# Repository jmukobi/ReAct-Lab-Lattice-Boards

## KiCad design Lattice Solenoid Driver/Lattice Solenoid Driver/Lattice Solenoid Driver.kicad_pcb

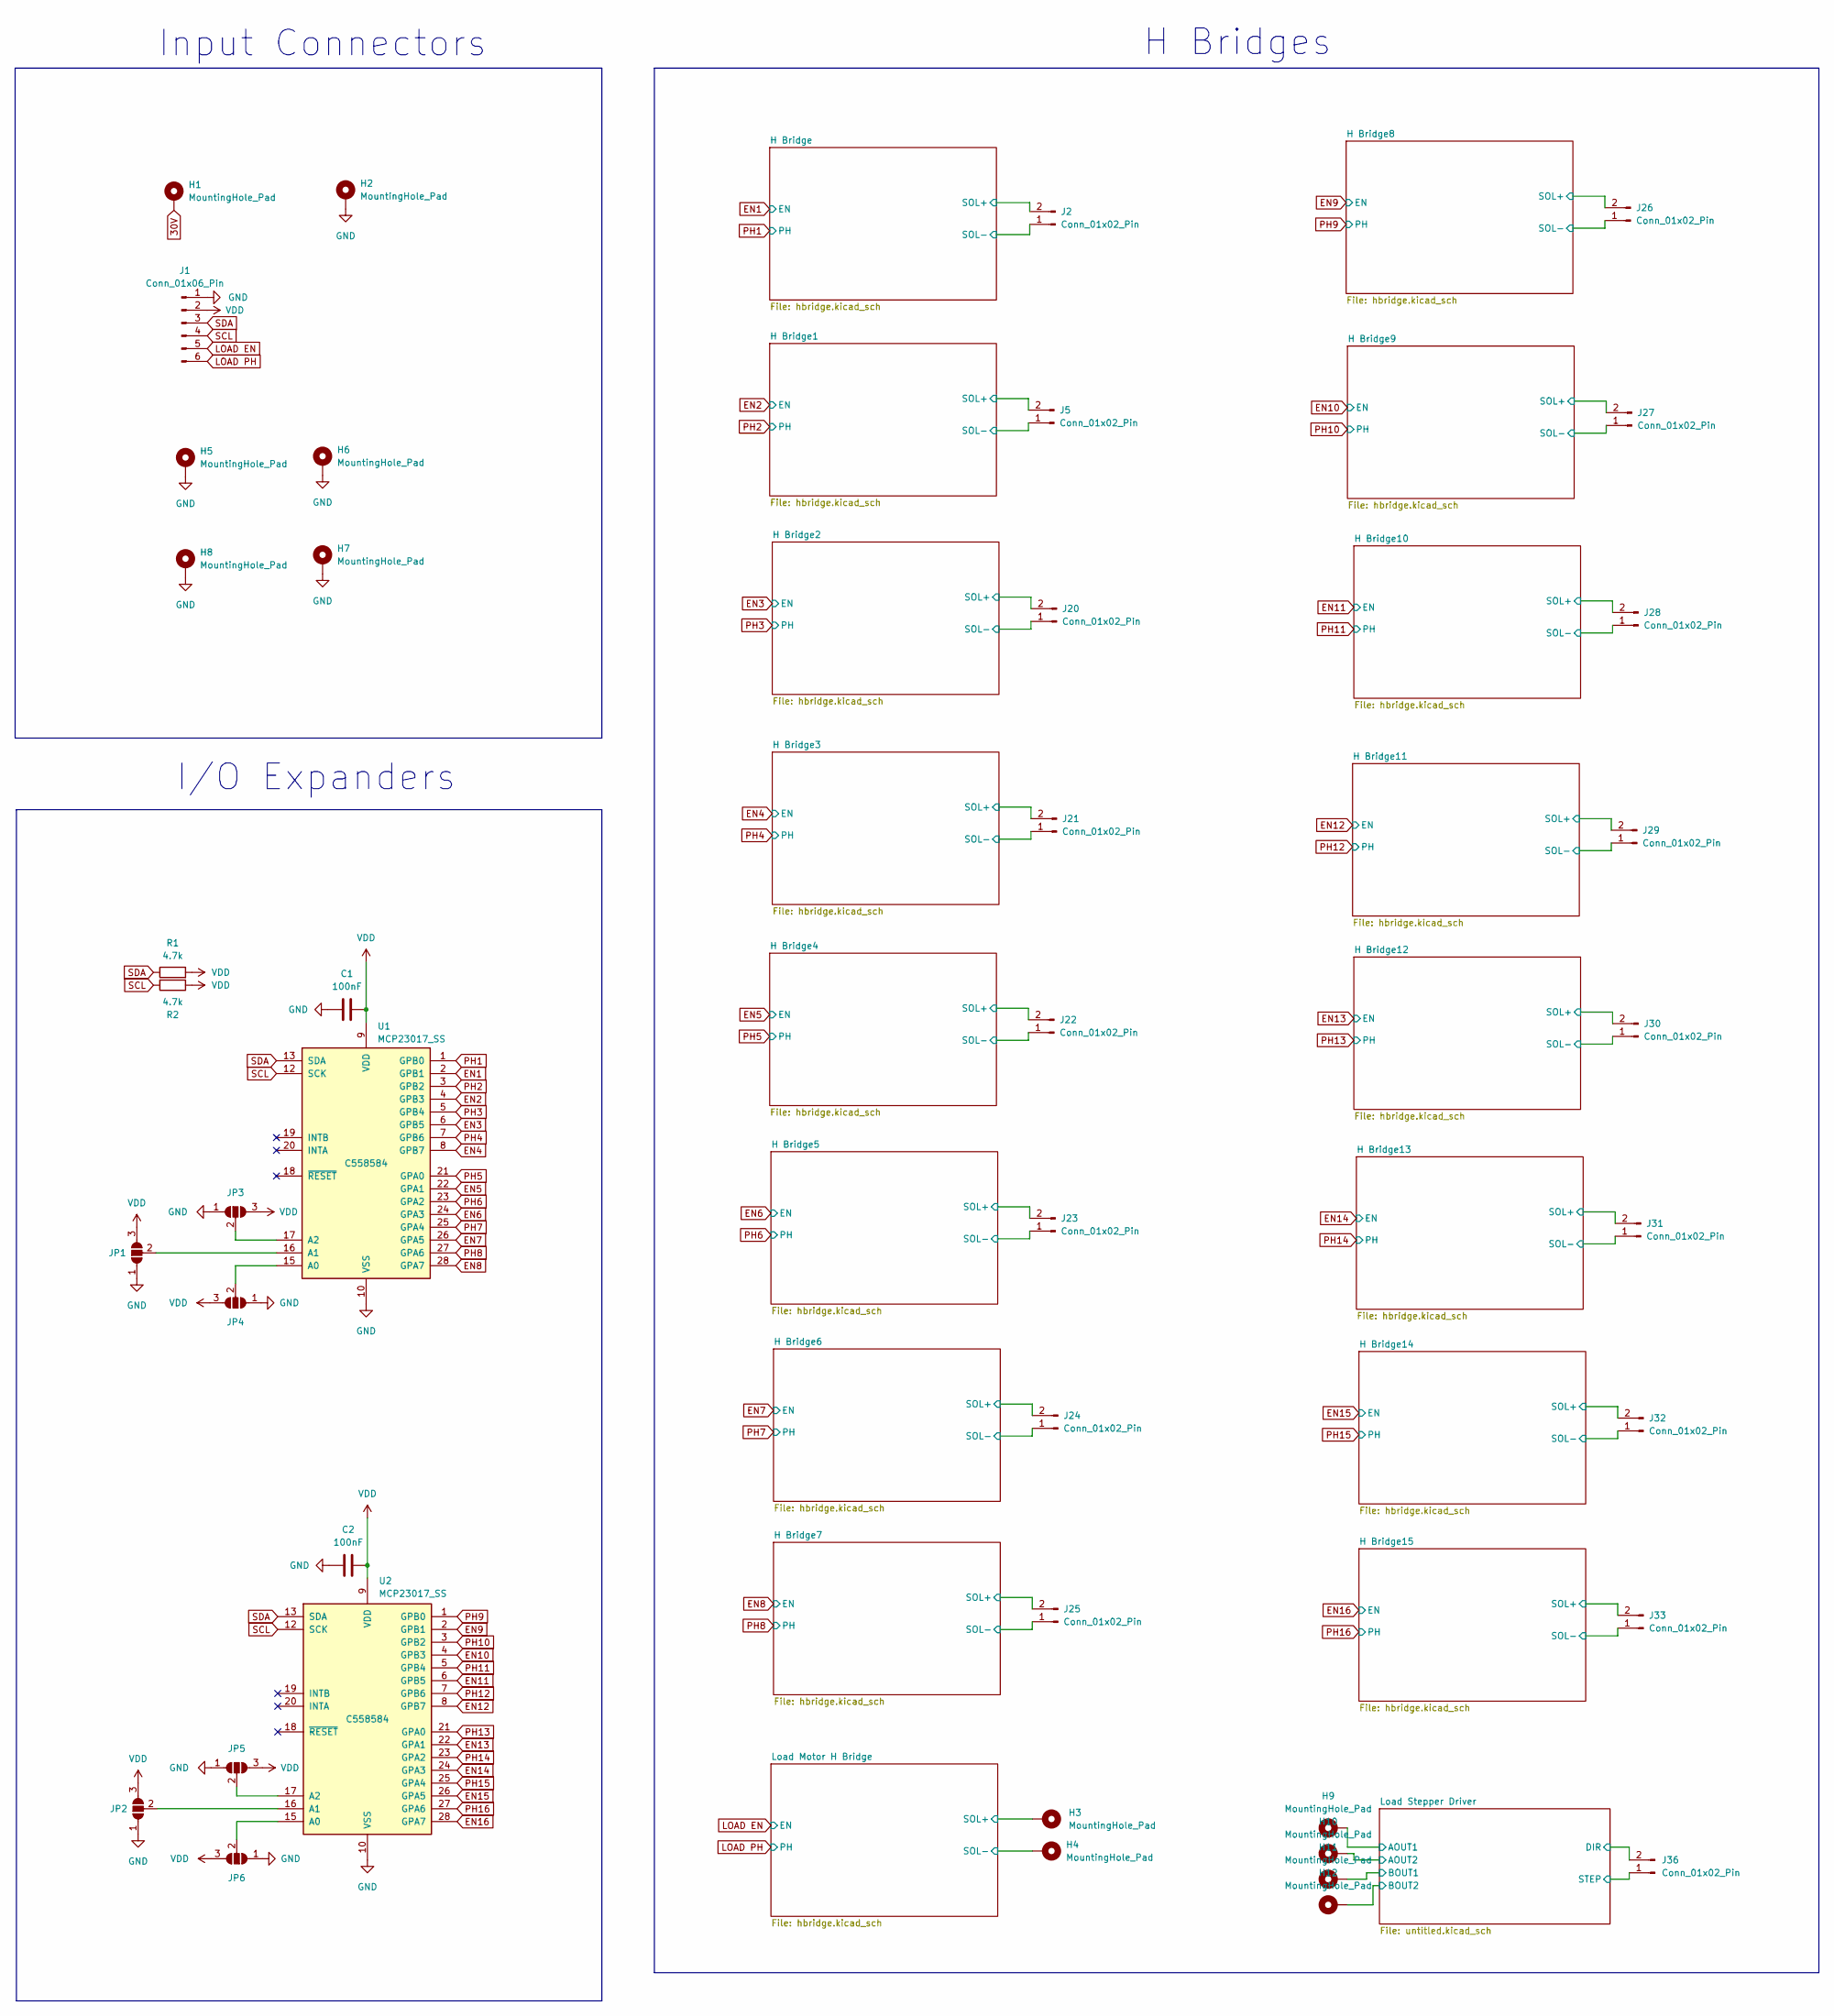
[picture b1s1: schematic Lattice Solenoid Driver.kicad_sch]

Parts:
C1, C2: 100nF; C_0805_2012Metric; Part # CC0805KRX7R9BB104
H1, H2, H3, H4, H5, H6, H7, H8, H9, H10, H11, H12: MountingHole_Pad; MountingHole_3.2mm_M3_DIN965_Pad_TopBottom
J1: Conn_01x06_Pin; PinHeader_1x06_P2.54mm_Vertical
J2, J5, J20, J21, J22, J23, J24, J25, J26, J27, J28, J29, J30, J31, J32, J33, J36: Conn_01x02_Pin; PinHeader_1x02_P2.54mm_Vertical
JP1, JP2, JP3, JP4, JP5, JP6: SolderJumper_3_Open; SolderJumper-3_P1.3mm_Open_RoundedPad1.0x1.5mm_NumberLabels
R1, R2: 4.7k; R_0805_2012Metric; Part # C17673
U1, U2: MCP23017_SS; SSOP-28_5.3x10.2mm_P0.65mm; Part # C558584

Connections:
30V: H1.1; also elsewhere on the board
/H Bridge1/SOL+: J5.2; also elsewhere on the board
/H Bridge1/SOL-: J5.1; also elsewhere on the board
/H Bridge2/SOL+: J20.2; also elsewhere on the board
/H Bridge2/SOL-: J20.1; also elsewhere on the board
/H Bridge3/SOL+: J21.2; also elsewhere on the board
/H Bridge3/SOL-: J21.1; also elsewhere on the board
/H Bridge4/SOL+: J22.2; also elsewhere on the board
/H Bridge4/SOL-: J22.1; also elsewhere on the board
/H Bridge5/SOL+: J23.2; also elsewhere on the board
/H Bridge5/SOL-: J23.1; also elsewhere on the board
/H Bridge6/SOL+: J24.2; also elsewhere on the board
/H Bridge6/SOL-: J24.1; also elsewhere on the board
/H Bridge7/SOL+: J25.2; also elsewhere on the board
/H Bridge7/SOL-: J25.1; also elsewhere on the board
/H Bridge8/SOL+: J26.2; also elsewhere on the board
/H Bridge8/SOL-: J26.1; also elsewhere on the board
/H Bridge9/SOL+: J27.2; also elsewhere on the board
/H Bridge9/SOL-: J27.1; also elsewhere on the board
/H Bridge10/SOL+: J28.2; also elsewhere on the board
/H Bridge10/SOL-: J28.1; also elsewhere on the board
/H Bridge11/SOL+: J29.2; also elsewhere on the board
/H Bridge11/SOL-: J29.1; also elsewhere on the board
/H Bridge12/SOL+: J30.2; also elsewhere on the board
/H Bridge12/SOL-: J30.1; also elsewhere on the board
/H Bridge13/SOL+: J31.2; also elsewhere on the board
/H Bridge13/SOL-: J31.1; also elsewhere on the board
/H Bridge14/SOL+: J32.2; also elsewhere on the board
/H Bridge14/SOL-: J32.1; also elsewhere on the board
/H Bridge15/SOL+: J33.2; also elsewhere on the board
/H Bridge15/SOL-: J33.1; also elsewhere on the board
/H Bridge/SOL+: J2.2; also elsewhere on the board
/H Bridge/SOL-: J2.1; also elsewhere on the board
/Load Motor H Bridge/SOL+: H3.1; also elsewhere on the board
/Load Motor H Bridge/SOL-: H4.1; also elsewhere on the board
/Load Stepper Driver/DIR: J36.2; also elsewhere on the board
/Load Stepper Driver/STEP: J36.1; also elsewhere on the board
EN1: U1.2 (GPB1); also elsewhere on the board
EN2: U1.4 (GPB3); also elsewhere on the board
EN3: U1.6 (GPB5); also elsewhere on the board
EN4: U1.8 (GPB7); also elsewhere on the board
EN5: U1.22 (GPA1); also elsewhere on the board
EN6: U1.24 (GPA3); also elsewhere on the board
EN7: U1.26 (GPA5); also elsewhere on the board
EN8: U1.28 (GPA7); also elsewhere on the board
EN9: U2.2 (GPB1); also elsewhere on the board
EN10: U2.4 (GPB3); also elsewhere on the board
EN11: U2.6 (GPB5); also elsewhere on the board
EN12: U2.8 (GPB7); also elsewhere on the board
EN13: U2.22 (GPA1); also elsewhere on the board
EN14: U2.24 (GPA3); also elsewhere on the board
EN15: U2.26 (GPA5); also elsewhere on the board
EN16: U2.28 (GPA7); also elsewhere on the board
GND: C1.1, C2.1, H2.1, H5.1, H6.1, H7.1, H8.1, J1.1, JP1.1 (A), JP2.1 (A), JP3.1 (A), JP4.1 (A), JP5.1 (A), JP6.1 (A), U1.10 (VSS), U2.10 (VSS); also elsewhere on the board
LOAD EN: J1.5; also elsewhere on the board
LOAD PH: J1.6; also elsewhere on the board
unnamed: JP1.2 (C), U1.16 (A1)
unnamed: JP2.2 (C), U2.16 (A1)
unnamed: JP3.2 (C), U1.17 (A2)
unnamed: JP4.2 (C), U1.15 (A0)
unnamed: JP5.2 (C), U2.17 (A2)
unnamed: JP6.2 (C), U2.15 (A0)
PH1: U1.1 (GPB0); also elsewhere on the board
PH2: U1.3 (GPB2); also elsewhere on the board
PH3: U1.5 (GPB4); also elsewhere on the board
PH4: U1.7 (GPB6); also elsewhere on the board
PH5: U1.21 (GPA0); also elsewhere on the board
PH6: U1.23 (GPA2); also elsewhere on the board
PH7: U1.25 (GPA4); also elsewhere on the board
PH8: U1.27 (GPA6); also elsewhere on the board
PH9: U2.1 (GPB0); also elsewhere on the board
PH10: U2.3 (GPB2); also elsewhere on the board
PH11: U2.5 (GPB4); also elsewhere on the board
PH12: U2.7 (GPB6); also elsewhere on the board
PH13: U2.21 (GPA0); also elsewhere on the board
PH14: U2.23 (GPA2); also elsewhere on the board
PH15: U2.25 (GPA4); also elsewhere on the board
PH16: U2.27 (GPA6); also elsewhere on the board
SCL: J1.4, R2.2, U1.12 (SCK), U2.12 (SCK)
SDA: J1.3, R1.1, U1.13 (SDA), U2.13 (SDA)
VDD: C1.2, C2.2, J1.2, JP1.3 (B), JP2.3 (B), JP3.3 (B), JP4.3 (B), JP5.3 (B), JP6.3 (B), R1.2, R2.1, U1.9 (VDD), U2.9 (VDD); also elsewhere on the board

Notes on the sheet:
H Bridges
I/O Expanders
Input Connectors

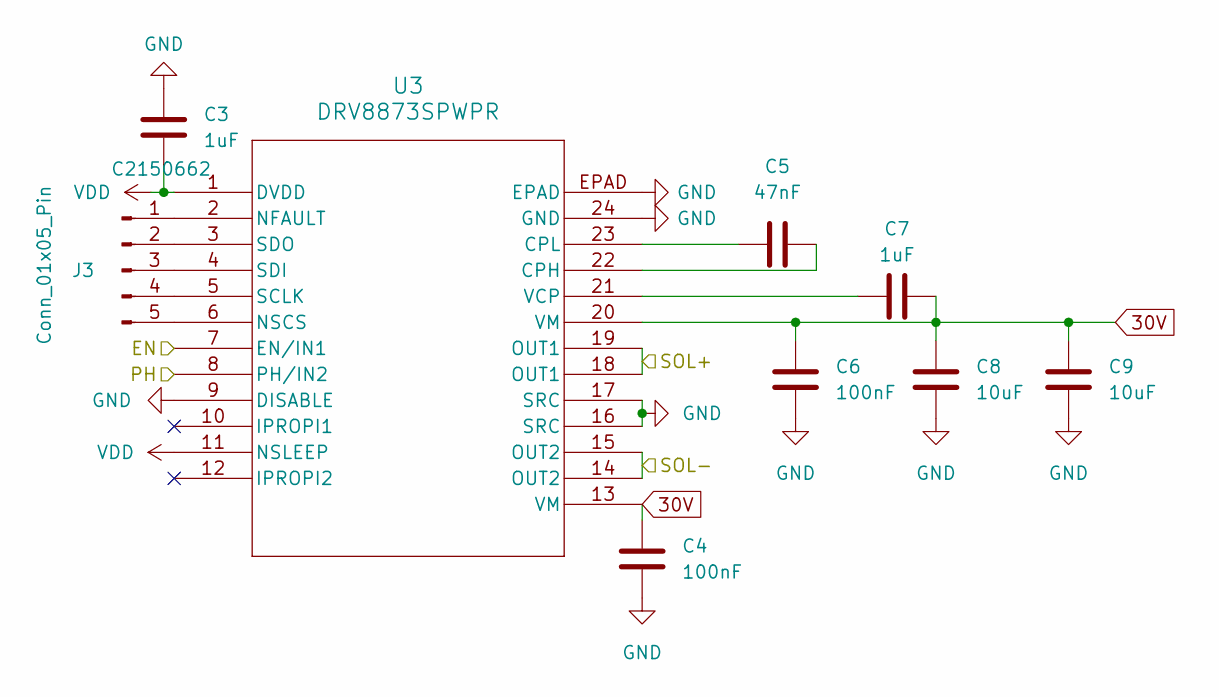
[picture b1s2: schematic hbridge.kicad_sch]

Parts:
C3, C7: 1uF; C_0805_2012Metric; Part # CL21B105KBFNNNE
C4, C6: 100nF; C_0805_2012Metric; Part # CC0805KRX7R9BB104
C5: 47nF; C_0805_2012Metric; Part # CL21B473KBCNNNC
C8, C9: 10uF; C_0805_2012Metric; Part # GRM21BR61H106KE43L
J3: Conn_01x05_Pin; PinHeader_1x05_P2.54mm_Vertical
U3: DRV8873SPWPR; PWP24_TEX; Part # C2150662

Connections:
30V: C4.1, C6.1, C7.2, C8.1, C9.1, U3.13 (VM), U3.20 (VM); also elsewhere on the board
/H Bridge/SOL+: U3.18 (OUT1), U3.19 (OUT1); also elsewhere on the board
/H Bridge/SOL-: U3.14 (OUT2), U3.15 (OUT2); also elsewhere on the board
EN1: U3.7 (EN/IN1); also elsewhere on the board
GND: C3.1, C4.2, C6.2, C8.2, C9.2, U3.9 (DISABLE), U3.16 (SRC), U3.17 (SRC), U3.24 (GND), U3.EPAD; also elsewhere on the board
unnamed: J3.1, U3.2 (NFAULT)
unnamed: J3.2, U3.3 (SDO)
unnamed: J3.3, U3.4 (SDI)
unnamed: J3.4, U3.5 (SCLK)
unnamed: J3.5, U3.6 (NSCS)
unnamed: C5.2, U3.22 (CPH)
unnamed: C5.1, U3.23 (CPL)
unnamed: C7.1, U3.21 (VCP)
PH1: U3.8 (PH/IN2); also elsewhere on the board
VDD: C3.2, U3.1 (DVDD), U3.11 (NSLEEP); also elsewhere on the board

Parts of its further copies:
C10, C14, C17, C21, C24, C28, C31, C35, C38, C42, C45, C49, C52, C56, C59, C63, C66, C70, C73, C77, C80, C84, C87, C91, C94, C98, C101, C105, C108, C112, C115, C119: 1uF; C_0805_2012Metric; Part # CL21B105KBFNNNE
C11, C13, C18, C20, C25, C27, C32, C34, C39, C41, C46, C48, C53, C55, C60, C62, C67, C69, C74, C76, C81, C83, C88, C90, C95, C97, C102, C104, C109, C111, C116, C118: 100nF; C_0805_2012Metric; Part # CC0805KRX7R9BB104
C12, C19, C26, C33, C40, C47, C54, C61, C68, C75, C82, C89, C96, C103, C110, C117: 47nF; C_0805_2012Metric; Part # CL21B473KBCNNNC
C15, C16, C22, C23, C29, C30, C36, C37, C43, C44, C50, C51, C57, C58, C64, C65, C71, C72, C78, C79, C85, C86, C92, C93, C99, C100, C106, C107, C113, C114, C120, C121: 10uF; C_0805_2012Metric; Part # GRM21BR61H106KE43L
J4, J6, J7, J8, J9, J10, J11, J12, J13, J14, J15, J16, J17, J18, J19, J34: Conn_01x05_Pin; PinHeader_1x05_P2.54mm_Vertical
U4, U5, U6, U7, U8, U9, U10, U11, U12, U13, U14, U15, U16, U17, U18, U19: DRV8873SPWPR; PWP24_TEX; Part # C2150662

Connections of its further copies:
30V: C11.1, C13.1, C14.2, C15.1, C16.1, C18.1, C20.1, C21.2, C22.1, C23.1, C25.1, C27.1, C28.2, C29.1, C30.1, C32.1, C34.1, C35.2, C36.1, C37.1, C39.1, C41.1, C42.2, C43.1, C44.1, C46.1, C48.1, C49.2, C50.1, C51.1, C53.1, C55.1, C56.2, C57.1, C58.1, C60.1, C62.1, C63.2, C64.1, C65.1, C67.1, C69.1, C70.2, C71.1, C72.1, C74.1, C76.1, C77.2, C78.1, C79.1, C81.1, C83.1, C84.2, C85.1, C86.1, C88.1, C90.1, C91.2, C92.1, C93.1, C95.1, C97.1, C98.2, C99.1, C100.1, C102.1, C104.1, C105.2, C106.1, C107.1, C109.1, C111.1, C112.2, C113.1, C114.1, C116.1, C118.1, C119.2, C120.1, C121.1, U4.13 (VM), U4.20 (VM), U5.13 (VM), U5.20 (VM), U6.13 (VM), U6.20 (VM), U7.13 (VM), U7.20 (VM), U8.13 (VM), U8.20 (VM), U9.13 (VM), U9.20 (VM), U10.13 (VM), U10.20 (VM), U11.13 (VM), U11.20 (VM), U12.13 (VM), U12.20 (VM), U13.13 (VM), U13.20 (VM), U14.13 (VM), U14.20 (VM), U15.13 (VM), U15.20 (VM), U16.13 (VM), U16.20 (VM), U17.13 (VM), U17.20 (VM), U18.13 (VM), U18.20 (VM), U19.13 (VM), U19.20 (VM); also elsewhere on the board
/H Bridge1/SOL+: U4.18 (OUT1), U4.19 (OUT1); also elsewhere on the board
/H Bridge1/SOL-: U4.14 (OUT2), U4.15 (OUT2); also elsewhere on the board
/H Bridge2/SOL+: U5.18 (OUT1), U5.19 (OUT1); also elsewhere on the board
/H Bridge2/SOL-: U5.14 (OUT2), U5.15 (OUT2); also elsewhere on the board
/H Bridge3/SOL+: U6.18 (OUT1), U6.19 (OUT1); also elsewhere on the board
/H Bridge3/SOL-: U6.14 (OUT2), U6.15 (OUT2); also elsewhere on the board
/H Bridge4/SOL+: U7.18 (OUT1), U7.19 (OUT1); also elsewhere on the board
/H Bridge4/SOL-: U7.14 (OUT2), U7.15 (OUT2); also elsewhere on the board
/H Bridge5/SOL+: U8.18 (OUT1), U8.19 (OUT1); also elsewhere on the board
/H Bridge5/SOL-: U8.14 (OUT2), U8.15 (OUT2); also elsewhere on the board
/H Bridge6/SOL+: U9.18 (OUT1), U9.19 (OUT1); also elsewhere on the board
/H Bridge6/SOL-: U9.14 (OUT2), U9.15 (OUT2); also elsewhere on the board
/H Bridge7/SOL+: U10.18 (OUT1), U10.19 (OUT1); also elsewhere on the board
/H Bridge7/SOL-: U10.14 (OUT2), U10.15 (OUT2); also elsewhere on the board
/H Bridge8/SOL+: U11.18 (OUT1), U11.19 (OUT1); also elsewhere on the board
/H Bridge8/SOL-: U11.14 (OUT2), U11.15 (OUT2); also elsewhere on the board
/H Bridge9/SOL+: U12.18 (OUT1), U12.19 (OUT1); also elsewhere on the board
/H Bridge9/SOL-: U12.14 (OUT2), U12.15 (OUT2); also elsewhere on the board
/H Bridge10/SOL+: U13.18 (OUT1), U13.19 (OUT1); also elsewhere on the board
/H Bridge10/SOL-: U13.14 (OUT2), U13.15 (OUT2); also elsewhere on the board
/H Bridge11/SOL+: U14.18 (OUT1), U14.19 (OUT1); also elsewhere on the board
/H Bridge11/SOL-: U14.14 (OUT2), U14.15 (OUT2); also elsewhere on the board
/H Bridge12/SOL+: U15.18 (OUT1), U15.19 (OUT1); also elsewhere on the board
/H Bridge12/SOL-: U15.14 (OUT2), U15.15 (OUT2); also elsewhere on the board
/H Bridge13/SOL+: U16.18 (OUT1), U16.19 (OUT1); also elsewhere on the board
/H Bridge13/SOL-: U16.14 (OUT2), U16.15 (OUT2); also elsewhere on the board
/H Bridge14/SOL+: U17.18 (OUT1), U17.19 (OUT1); also elsewhere on the board
/H Bridge14/SOL-: U17.14 (OUT2), U17.15 (OUT2); also elsewhere on the board
/H Bridge15/SOL+: U18.18 (OUT1), U18.19 (OUT1); also elsewhere on the board
/H Bridge15/SOL-: U18.14 (OUT2), U18.15 (OUT2); also elsewhere on the board
/Load Motor H Bridge/SOL+: U19.18 (OUT1), U19.19 (OUT1); also elsewhere on the board
/Load Motor H Bridge/SOL-: U19.14 (OUT2), U19.15 (OUT2); also elsewhere on the board
EN2: U4.7 (EN/IN1); also elsewhere on the board
EN3: U5.7 (EN/IN1); also elsewhere on the board
EN4: U6.7 (EN/IN1); also elsewhere on the board
EN5: U7.7 (EN/IN1); also elsewhere on the board
EN6: U8.7 (EN/IN1); also elsewhere on the board
EN7: U9.7 (EN/IN1); also elsewhere on the board
EN8: U10.7 (EN/IN1); also elsewhere on the board
EN9: U11.7 (EN/IN1); also elsewhere on the board
EN10: U12.7 (EN/IN1); also elsewhere on the board
EN11: U13.7 (EN/IN1); also elsewhere on the board
EN12: U14.7 (EN/IN1); also elsewhere on the board
EN13: U15.7 (EN/IN1); also elsewhere on the board
EN14: U16.7 (EN/IN1); also elsewhere on the board
EN15: U17.7 (EN/IN1); also elsewhere on the board
EN16: U18.7 (EN/IN1); also elsewhere on the board
GND: C10.1, C11.2, C13.2, C15.2, C16.2, C17.1, C18.2, C20.2, C22.2, C23.2, C24.1, C25.2, C27.2, C29.2, C30.2, C31.1, C32.2, C34.2, C36.2, C37.2, C38.1, C39.2, C41.2, C43.2, C44.2, C45.1, C46.2, C48.2, C50.2, C51.2, C52.1, C53.2, C55.2, C57.2, C58.2, C59.1, C60.2, C62.2, C64.2, C65.2, C66.1, C67.2, C69.2, C71.2, C72.2, C73.1, C74.2, C76.2, C78.2, C79.2, C80.1, C81.2, C83.2, C85.2, C86.2, C87.1, C88.2, C90.2, C92.2, C93.2, C94.1, C95.2, C97.2, C99.2, C100.2, C101.1, C102.2, C104.2, C106.2, C107.2, C108.1, C109.2, C111.2, C113.2, C114.2, C115.1, C116.2, C118.2, C120.2, C121.2, U4.9 (DISABLE), U4.16 (SRC), U4.17 (SRC), U4.24 (GND), U4.EPAD, U5.9 (DISABLE), U5.16 (SRC), U5.17 (SRC), U5.24 (GND), U5.EPAD, U6.9 (DISABLE), U6.16 (SRC), U6.17 (SRC), U6.24 (GND), U6.EPAD, U7.9 (DISABLE), U7.16 (SRC), U7.17 (SRC), U7.24 (GND), U7.EPAD, U8.9 (DISABLE), U8.16 (SRC), U8.17 (SRC), U8.24 (GND), U8.EPAD, U9.9 (DISABLE), U9.16 (SRC), U9.17 (SRC), U9.24 (GND), U9.EPAD, U10.9 (DISABLE), U10.16 (SRC), U10.17 (SRC), U10.24 (GND), U10.EPAD, U11.9 (DISABLE), U11.16 (SRC), U11.17 (SRC), U11.24 (GND), U11.EPAD, U12.9 (DISABLE), U12.16 (SRC), U12.17 (SRC), U12.24 (GND), U12.EPAD, U13.9 (DISABLE), U13.16 (SRC), U13.17 (SRC), U13.24 (GND), U13.EPAD, U14.9 (DISABLE), U14.16 (SRC), U14.17 (SRC), U14.24 (GND), U14.EPAD, U15.9 (DISABLE), U15.16 (SRC), U15.17 (SRC), U15.24 (GND), U15.EPAD, U16.9 (DISABLE), U16.16 (SRC), U16.17 (SRC), U16.24 (GND), U16.EPAD, U17.9 (DISABLE), U17.16 (SRC), U17.17 (SRC), U17.24 (GND), U17.EPAD, U18.9 (DISABLE), U18.16 (SRC), U18.17 (SRC), U18.24 (GND), U18.EPAD, U19.9 (DISABLE), U19.16 (SRC), U19.17 (SRC), U19.24 (GND), U19.EPAD; also elsewhere on the board
LOAD EN: U19.7 (EN/IN1); also elsewhere on the board
LOAD PH: U19.8 (PH/IN2); also elsewhere on the board
unnamed: J4.1, U4.2 (NFAULT)
unnamed: J4.2, U4.3 (SDO)
unnamed: J4.3, U4.4 (SDI)
unnamed: J4.4, U4.5 (SCLK)
unnamed: J4.5, U4.6 (NSCS)
unnamed: J6.1, U5.2 (NFAULT)
unnamed: J6.2, U5.3 (SDO)
unnamed: J6.3, U5.4 (SDI)
unnamed: J6.4, U5.5 (SCLK)
unnamed: J6.5, U5.6 (NSCS)
unnamed: J7.1, U6.2 (NFAULT)
unnamed: J7.2, U6.3 (SDO)
unnamed: J7.3, U6.4 (SDI)
unnamed: J7.4, U6.5 (SCLK)
unnamed: J7.5, U6.6 (NSCS)
unnamed: J8.1, U7.2 (NFAULT)
unnamed: J8.2, U7.3 (SDO)
unnamed: J8.3, U7.4 (SDI)
unnamed: J8.4, U7.5 (SCLK)
unnamed: J8.5, U7.6 (NSCS)
unnamed: J9.1, U8.2 (NFAULT)
unnamed: J9.2, U8.3 (SDO)
unnamed: J9.3, U8.4 (SDI)
unnamed: J9.4, U8.5 (SCLK)
unnamed: J9.5, U8.6 (NSCS)
unnamed: J10.1, U9.2 (NFAULT)
unnamed: J10.2, U9.3 (SDO)
unnamed: J10.3, U9.4 (SDI)
unnamed: J10.4, U9.5 (SCLK)
unnamed: J10.5, U9.6 (NSCS)
unnamed: J11.1, U10.2 (NFAULT)
unnamed: J11.2, U10.3 (SDO)
unnamed: J11.3, U10.4 (SDI)
unnamed: J11.4, U10.5 (SCLK)
unnamed: J11.5, U10.6 (NSCS)
unnamed: J12.1, U11.2 (NFAULT)
unnamed: J12.2, U11.3 (SDO)
unnamed: J12.3, U11.4 (SDI)
unnamed: J12.4, U11.5 (SCLK)
unnamed: J12.5, U11.6 (NSCS)
unnamed: J13.1, U12.2 (NFAULT)
unnamed: J13.2, U12.3 (SDO)
unnamed: J13.3, U12.4 (SDI)
unnamed: J13.4, U12.5 (SCLK)
unnamed: J13.5, U12.6 (NSCS)
unnamed: J14.1, U13.2 (NFAULT)
unnamed: J14.2, U13.3 (SDO)
unnamed: J14.3, U13.4 (SDI)
unnamed: J14.4, U13.5 (SCLK)
unnamed: J14.5, U13.6 (NSCS)
unnamed: J15.1, U14.2 (NFAULT)
unnamed: J15.2, U14.3 (SDO)
unnamed: J15.3, U14.4 (SDI)
unnamed: J15.4, U14.5 (SCLK)
unnamed: J15.5, U14.6 (NSCS)
unnamed: J16.1, U15.2 (NFAULT)
unnamed: J16.2, U15.3 (SDO)
unnamed: J16.3, U15.4 (SDI)
unnamed: J16.4, U15.5 (SCLK)
unnamed: J16.5, U15.6 (NSCS)
unnamed: J17.1, U16.2 (NFAULT)
unnamed: J17.2, U16.3 (SDO)
unnamed: J17.3, U16.4 (SDI)
unnamed: J17.4, U16.5 (SCLK)
unnamed: J17.5, U16.6 (NSCS)
unnamed: J18.1, U17.2 (NFAULT)
unnamed: J18.2, U17.3 (SDO)
unnamed: J18.3, U17.4 (SDI)
unnamed: J18.4, U17.5 (SCLK)
unnamed: J18.5, U17.6 (NSCS)
unnamed: J19.1, U18.2 (NFAULT)
unnamed: J19.2, U18.3 (SDO)
unnamed: J19.3, U18.4 (SDI)
unnamed: J19.4, U18.5 (SCLK)
unnamed: J19.5, U18.6 (NSCS)
unnamed: J34.1, U19.2 (NFAULT)
unnamed: J34.2, U19.3 (SDO)
unnamed: J34.3, U19.4 (SDI)
unnamed: J34.4, U19.5 (SCLK)
unnamed: J34.5, U19.6 (NSCS)
unnamed: C12.2, U4.22 (CPH)
unnamed: C12.1, U4.23 (CPL)
unnamed: C14.1, U4.21 (VCP)
unnamed: C19.2, U5.22 (CPH)
unnamed: C19.1, U5.23 (CPL)
unnamed: C21.1, U5.21 (VCP)
unnamed: C26.2, U6.22 (CPH)
unnamed: C26.1, U6.23 (CPL)
unnamed: C28.1, U6.21 (VCP)
unnamed: C33.2, U7.22 (CPH)
unnamed: C33.1, U7.23 (CPL)
unnamed: C35.1, U7.21 (VCP)
unnamed: C40.2, U8.22 (CPH)
unnamed: C40.1, U8.23 (CPL)
unnamed: C42.1, U8.21 (VCP)
unnamed: C47.2, U9.22 (CPH)
unnamed: C47.1, U9.23 (CPL)
unnamed: C49.1, U9.21 (VCP)
unnamed: C54.2, U10.22 (CPH)
unnamed: C54.1, U10.23 (CPL)
unnamed: C56.1, U10.21 (VCP)
unnamed: C61.2, U11.22 (CPH)
unnamed: C61.1, U11.23 (CPL)
unnamed: C63.1, U11.21 (VCP)
unnamed: C68.2, U12.22 (CPH)
unnamed: C68.1, U12.23 (CPL)
unnamed: C70.1, U12.21 (VCP)
unnamed: C75.2, U13.22 (CPH)
unnamed: C75.1, U13.23 (CPL)
unnamed: C77.1, U13.21 (VCP)
unnamed: C82.2, U14.22 (CPH)
unnamed: C82.1, U14.23 (CPL)
unnamed: C84.1, U14.21 (VCP)
unnamed: C89.2, U15.22 (CPH)
unnamed: C89.1, U15.23 (CPL)
unnamed: C91.1, U15.21 (VCP)
unnamed: C96.2, U16.22 (CPH)
unnamed: C96.1, U16.23 (CPL)
unnamed: C98.1, U16.21 (VCP)
unnamed: C103.2, U17.22 (CPH)
unnamed: C103.1, U17.23 (CPL)
unnamed: C105.1, U17.21 (VCP)
unnamed: C110.2, U18.22 (CPH)
unnamed: C110.1, U18.23 (CPL)
unnamed: C112.1, U18.21 (VCP)
unnamed: C117.2, U19.22 (CPH)
unnamed: C117.1, U19.23 (CPL)
unnamed: C119.1, U19.21 (VCP)
PH2: U4.8 (PH/IN2); also elsewhere on the board
PH3: U5.8 (PH/IN2); also elsewhere on the board
PH4: U6.8 (PH/IN2); also elsewhere on the board
PH5: U7.8 (PH/IN2); also elsewhere on the board
PH6: U8.8 (PH/IN2); also elsewhere on the board
PH7: U9.8 (PH/IN2); also elsewhere on the board
PH8: U10.8 (PH/IN2); also elsewhere on the board
PH9: U11.8 (PH/IN2); also elsewhere on the board
PH10: U12.8 (PH/IN2); also elsewhere on the board
PH11: U13.8 (PH/IN2); also elsewhere on the board
PH12: U14.8 (PH/IN2); also elsewhere on the board
PH13: U15.8 (PH/IN2); also elsewhere on the board
PH14: U16.8 (PH/IN2); also elsewhere on the board
PH15: U17.8 (PH/IN2); also elsewhere on the board
PH16: U18.8 (PH/IN2); also elsewhere on the board
VDD: C10.2, C17.2, C24.2, C31.2, C38.2, C45.2, C52.2, C59.2, C66.2, C73.2, C80.2, C87.2, C94.2, C101.2, C108.2, C115.2, U4.1 (DVDD), U4.11 (NSLEEP), U5.1 (DVDD), U5.11 (NSLEEP), U6.1 (DVDD), U6.11 (NSLEEP), U7.1 (DVDD), U7.11 (NSLEEP), U8.1 (DVDD), U8.11 (NSLEEP), U9.1 (DVDD), U9.11 (NSLEEP), U10.1 (DVDD), U10.11 (NSLEEP), U11.1 (DVDD), U11.11 (NSLEEP), U12.1 (DVDD), U12.11 (NSLEEP), U13.1 (DVDD), U13.11 (NSLEEP), U14.1 (DVDD), U14.11 (NSLEEP), U15.1 (DVDD), U15.11 (NSLEEP), U16.1 (DVDD), U16.11 (NSLEEP), U17.1 (DVDD), U17.11 (NSLEEP), U18.1 (DVDD), U18.11 (NSLEEP), U19.1 (DVDD), U19.11 (NSLEEP); also elsewhere on the board

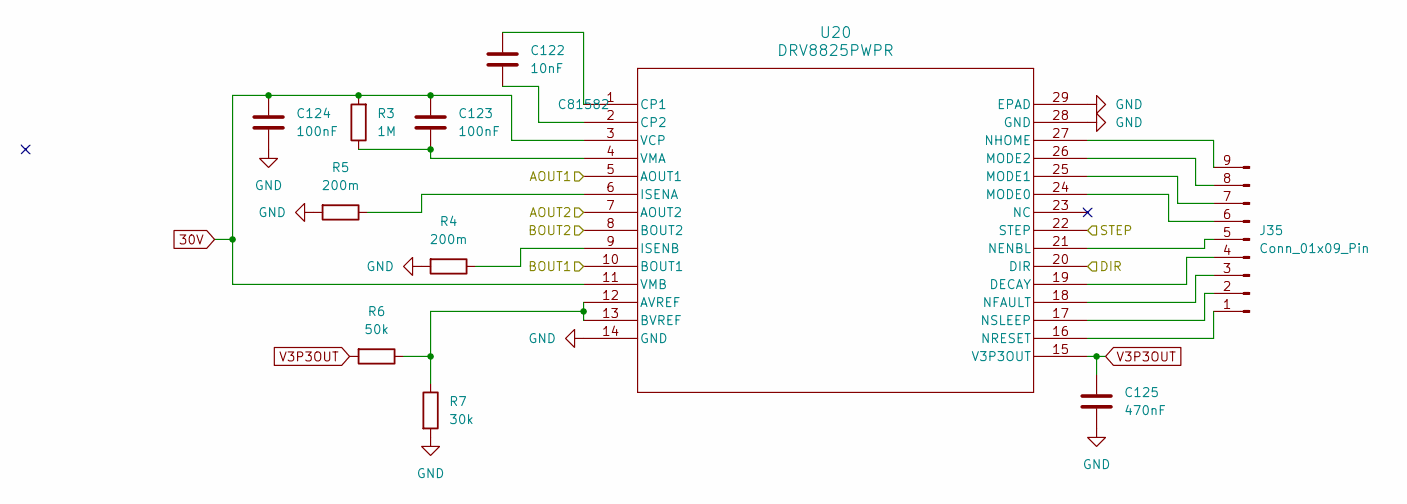
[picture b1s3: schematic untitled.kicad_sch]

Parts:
C122: 10nF; C_0805_2012Metric; Part # CC0805KRX7R9BB104
C123, C124: 100nF; C_0805_2012Metric; Part # CC0805KRX7R9BB104
C125: 470nF; C_0805_2012Metric; Part # CC0805KRX7R9BB104
J35: Conn_01x09_Pin; PinHeader_1x09_P2.54mm_Vertical
R3: 1M; R_0805_2012Metric; Part # C17673
R4, R5: 200m; R_0805_2012Metric; Part # C17673
R6: 50k; R_0805_2012Metric; Part # C17673
R7: 30k; R_0805_2012Metric; Part # C17673
U20: DRV8825PWPR; PWP28_5P18X3P1; Part # C81582

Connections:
30V: C123.1, C124.1, R3.2, U20.3 (VCP), U20.11 (VMB); also elsewhere on the board
/Load Stepper Driver/AOUT1: U20.5 (AOUT1); also elsewhere on the board
/Load Stepper Driver/AOUT2: U20.7 (AOUT2); also elsewhere on the board
/Load Stepper Driver/BOUT1: U20.10 (BOUT1); also elsewhere on the board
/Load Stepper Driver/BOUT2: U20.8 (BOUT2); also elsewhere on the board
/Load Stepper Driver/DIR: U20.20 (DIR); also elsewhere on the board
/Load Stepper Driver/STEP: U20.22 (STEP); also elsewhere on the board
GND: C124.2, C125.2, R4.2, R5.2, R7.2, U20.14 (GND), U20.28 (GND), U20.29 (EPAD); also elsewhere on the board
unnamed: J35.1, U20.16 (NRESET)
unnamed: J35.2, U20.17 (NSLEEP)
unnamed: J35.3, U20.18 (NFAULT)
unnamed: J35.4, U20.19 (DECAY)
unnamed: J35.5, U20.21 (NENBL)
unnamed: J35.6, U20.24 (MODE0)
unnamed: J35.7, U20.25 (MODE1)
unnamed: J35.8, U20.26 (MODE2)
unnamed: J35.9, U20.27 (NHOME)
unnamed: R6.1, R7.1, U20.12 (AVREF), U20.13 (BVREF)
unnamed: C122.1, U20.1 (CP1)
unnamed: C122.2, U20.2 (CP2)
unnamed: R5.1, U20.6 (ISENA)
unnamed: R4.1, U20.9 (ISENB)
unnamed: C123.2, R3.1, U20.4 (VMA)
V3P3OUT: C125.1, R6.2, U20.15 (V3P3OUT)

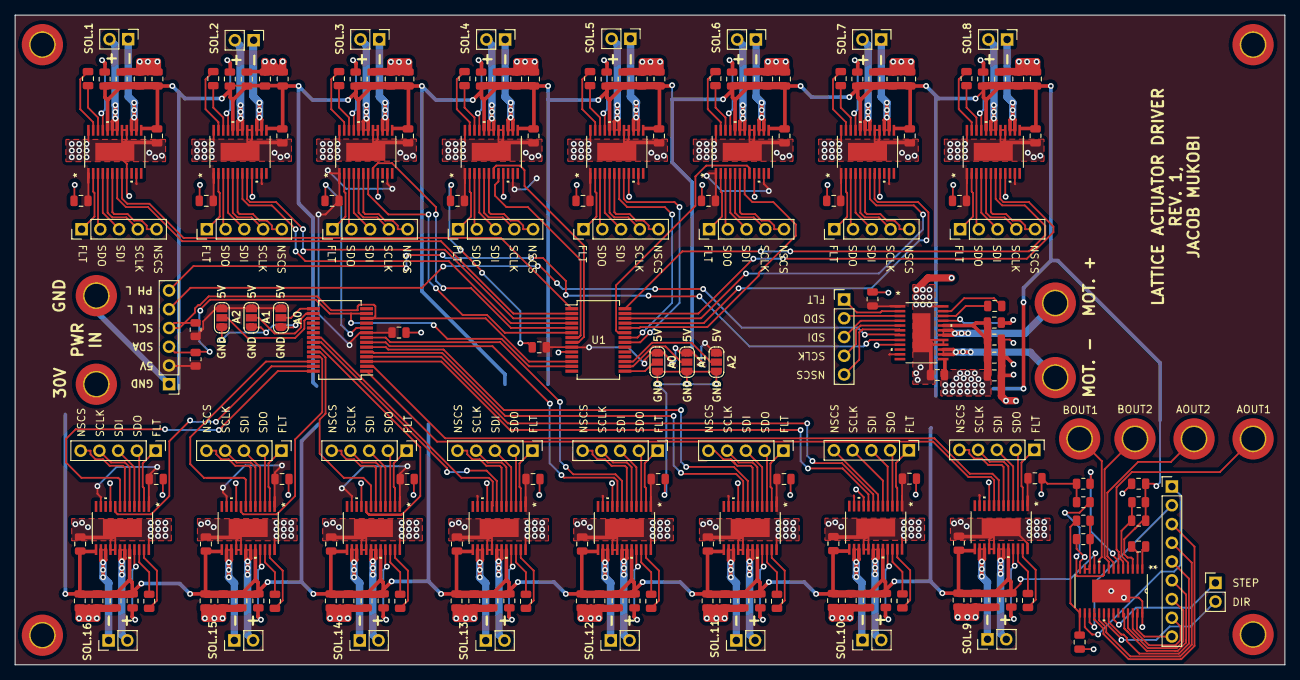
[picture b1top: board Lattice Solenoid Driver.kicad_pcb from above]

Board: 2 copper layers, 172.0 x 88.0 mm, 206 parts (0 on the bottom side), 237 nets.

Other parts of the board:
AOUT1, AOUT2: MountingHole_Pad; MountingHole_3.2mm_M3_DIN965_Pad_TopBottom
BOUT1, BOUT2: MountingHole_Pad; MountingHole_3.2mm_M3_DIN965_Pad_TopBottom

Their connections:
/Load Stepper Driver/AOUT1: AOUT1.1; also elsewhere on the board
/Load Stepper Driver/AOUT2: AOUT2.1; also elsewhere on the board
/Load Stepper Driver/BOUT1: BOUT1.1; also elsewhere on the board
/Load Stepper Driver/BOUT2: BOUT2.1; also elsewhere on the board

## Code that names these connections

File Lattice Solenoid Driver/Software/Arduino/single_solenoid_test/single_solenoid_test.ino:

#include <Wire.h>

// MCP23017 I2C addresses
#define MCP1_ADDR 0x26
#define MCP2_ADDR 0x24

// MCP23017 register addresses
#define IODIRA 0x00
#define IODIRB 0x01
#define OLATA  0x14
#define OLATB  0x15

// Struct to define each solenoid's PHASE and ENABLE pins
struct HBridgeControl {
  uint8_t expander;
  uint8_t phase_reg;
  uint8_t phase_bit;
  uint8_t enable_reg;
  uint8_t enable_bit;
};

// Define the mapping for each solenoid
HBridgeControl bridges[16] = {
  { MCP1_ADDR, OLATB, 0, OLATB, 1 }, // PH1, EN1
  { MCP1_ADDR, OLATB, 2, OLATB, 3 }, // PH2, EN2
  { MCP1_ADDR, OLATB, 4, OLATB, 5 }, // PH3, EN3
  { MCP1_ADDR, OLATB, 6, OLATB, 7 }, // PH4, EN4
  { MCP1_ADDR, OLATA, 0, OLATA, 1 }, // PH5, EN5
  { MCP1_ADDR, OLATA, 2, OLATA, 3 }, // PH6, EN6
  { MCP1_ADDR, OLATA, 4, OLATA, 5 }, // PH7, EN7
  { MCP1_ADDR, OLATA, 6, OLATA, 7 }, // PH8, EN8
  { MCP2_ADDR, OLATB, 0, OLATB, 1 }, // PH9, EN9
  { MCP2_ADDR, OLATB, 2, OLATB, 3 }, // PH10, EN10
  { MCP2_ADDR, OLATB, 4, OLATB, 5 }, // PH11, EN11
  { MCP2_ADDR, OLATB, 6, OLATB, 7 }, // PH12, EN12
  { MCP2_ADDR, OLATA, 0, OLATA, 1 }, // PH13, EN13
  { MCP2_ADDR, OLATA, 2, OLATA, 3 }, // PH14, EN14
  { MCP2_ADDR, OLATA, 4, OLATA, 5 }, // PH15, EN15
  { MCP2_ADDR, OLATA, 6, OLATA, 7 }  // PH16, EN16
};

void setup() {
  Serial.begin(115200);
  Wire.begin();

  // Initialize both expanders
  initExpander(MCP1_ADDR);
  initExpander(MCP2_ADDR);
}

void loop() {
  Serial.println("H-Bridge #10 FORWARD");
  setBridge(bridges[9], "forward"); // H-Bridge #10 corresponds to index 9
  delay(1); // 0.001s ON

  Serial.println("H-Bridge #9 OFF");
  setBridge(bridges[9], "off");
  delay(50);
  // set # 11 forward
  Serial.println("H-Bridge #11 FORWARD");
  setBridge(bridges[10], "forward"); // H-Bridge #11 corresponds to index 10
  delay(1); // 0.001s ON


  Serial.println("H-Bridge #11 OFF");
  setBridge(bridges[10], "off");
  delay(50);
  // set # 12 forward
  Serial.println("H-Bridge #12 FORWARD");
  setBridge(bridges[11], "forward"); // H-Bridge #12 corresponds to index 11
  delay(1); // 0.001s ON


  Serial.println("H-Bridge #12 OFF");
  setBridge(bridges[11], "off");
  delay(50);
  delay(500); // 4s OFF

  Serial.println("H-Bridge #9 REVERSE");
  setBridge(bridges[9], "reverse");
  delay(1); // 0.001s ON

  Serial.println("H-Bridge #9 OFF");
  setBridge(bridges[9], "off");
  delay(50);
  // set # 10 reverse
  Serial.println("H-Bridge #10 REVERSE");
  setBridge(bridges[10], "reverse"); // H-Bridge #10 corresponds to index 9

  delay(1); // 0.001s ON

  Serial.println("H-Bridge #10 OFF");
  setBridge(bridges[10], "off");
  delay(50);
  // set # 11 reverse

  Serial.println("H-Bridge #11 REVERSE");
  setBridge(bridges[11], "reverse"); // H-Bridge #11 corresponds to index 10

  delay(1); // 0.001s ON
  

  Serial.println("H-Bridge #11 OFF");
  setBridge(bridges[11], "off");
  

  delay(500); // 10s OFF
}

// === Control Functions ===

void initExpander(uint8_t addr) {
  writeRegister(addr, IODIRA, 0x00); // All A = output
  writeRegister(addr, IODIRB, 0x00); // All B = output
  writeRegister(addr, OLATA, 0x00);  // Clear outputs
  writeRegister(addr, OLATB, 0x00);
}

void setAllBridges(const char* mode) {
  for (int i = 0; i < 16; i++) {
    setBridge(bridges[10], mode);
  }
}

void setBridge(HBridgeControl hb, const char* mode) {
  if (strcmp(mode, "forward") == 0) {
    setPin(hb.expander, hb.phase_reg, hb.phase_bit, true);   // PH = 1
    setPin(hb.expander, hb.enable_reg, hb.enable_bit, false); // EN = 0
  } else if (strcmp(mode, "reverse") == 0) {
    setPin(hb.expander, hb.phase_reg, hb.phase_bit, false);  // PH = 0
    setPin(hb.expander, hb.enable_reg, hb.enable_bit, true);  // EN = 1
  } else { // "off"
    setPin(hb.expander, hb.phase_reg, hb.phase_bit, false);  // PH = 0
    setPin(hb.expander, hb.enable_reg, hb.enable_bit, false); // EN = 0 (Hi-Z)
  }
}

void setPin(uint8_t addr, uint8_t reg, uint8_t bit, bool value) {
  Serial.print("Setting pin: ");
  Serial.print("Addr: 0x");
  Serial.print(addr, HEX);
  Serial.print(", Reg: 0x");
  Serial.print(reg, HEX);
  Serial.print(", Bit: ");
  Serial.print(bit);
  Serial.print(", Value: ");
  Serial.println(value);

  Wire.beginTransmission(addr);
  Wire.write(reg);
  Wire.endTransmission(false); // Repeated start

  Wire.requestFrom(addr, (uint8_t)1);
  uint8_t current = Wire.read();

  uint8_t updated = value ? (current | (1 << bit)) : (current & ~(1 << bit));
  writeRegister(addr, reg, updated);
}

void writeRegister(uint8_t addr, uint8_t reg, uint8_t value) {
  Wire.beginTransmission(addr);
  Wire.write(reg);
  Wire.write(value);
  Wire.endTransmission();
}

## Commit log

2025-02-08 minor changes
2025-02-08 added code
2025-02-12 Rev1 mostly done
2025-02-25 Finished Rev 1 initial
2025-03-06 finishing touches
2025-03-07 adding stepper driver
2025-03-07 added stepper sch
2025-03-07 Final Stepper Edits
2025-03-08 grbrs
2025-04-12 started coding for the arduino
2025-04-14 metro mini testing
2025-04-14 stepper test
2025-05-01 more coding
